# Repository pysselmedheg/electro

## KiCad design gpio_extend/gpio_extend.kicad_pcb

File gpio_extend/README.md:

# GPIO Extender

This is a gpio extender using the good ol' trick with a 74xx595 shift register for output, and 74xx165 shift register for input. The intended usage is as debug output for a Raspberry Pi Pico, but it can of course be used with other mcus.

## GP Output

The output is (up to) 32 bit, arranged as 4 bytes. There is a R2R-DAC for each byte and a pin socket with the byte as digital and analog. There is also a LED for each bit.

## GP Input

The input is (up to) 32 bit, arranged as 4 bytes. Each byte has a pin socket, and a jumper to set pull up or down for the byte.

## Serial interface

The serial interface has four digital pins:
  - pclk    : frame sync
  - sclk    : serial clock
  - ser_in  : input into the gpio extender (for GPO)
  - ser_out : output from the gpio extender (for GPI)

Negative edge on pclk:
  - GPIs are sampled.
  
Positive edge on sclk:
  - GPI data is shifted out from the GPIO extender.
  - GPO data is shifted in to the GPIO extender.
  
Positive edge on pclk:
  - GPOs are updated with new data.

## Python Driver

The python folder contains a driver for Micropython on Raspberry Pi Pico. It uses two state machines in a PIO for the communication.
Surprisingly, it can handle the interface at cpu_clk/3 bps, ie 125MHz/3 = 41.7 MHz. 

TODO: Description of driver. Until then RTFS.

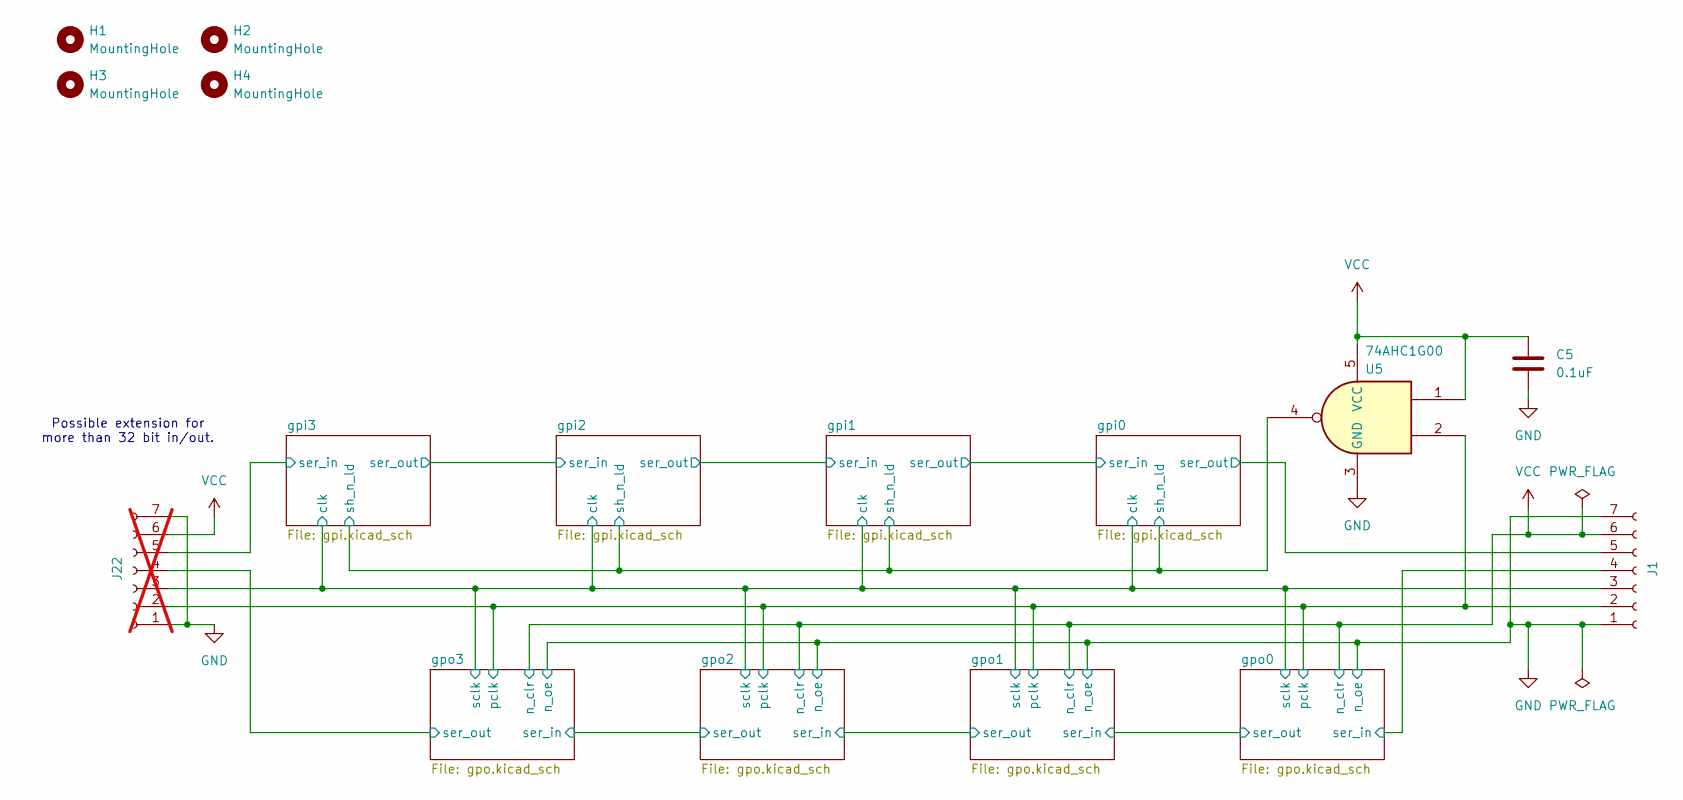
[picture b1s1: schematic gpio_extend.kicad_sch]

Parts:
C5: 0.1uF; C_0603_1608Metric_Pad1.08x0.95mm_HandSolder
H1, H2, H3, H4: MountingHole; MountingHole_3.2mm_M3
J1: Conn_01x07_Socket; PinSocket_1x07_P2.54mm_Vertical
J22: Conn_01x07_Socket; PinSocket_1x07_P2.54mm_Vertical; not fitted
U5: 74AHC1G00; SOT-23-5_HandSoldering

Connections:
/gpi0/clk: J1.3, J22.3; also elsewhere on the board
/gpi0/ser_out: J1.5; also elsewhere on the board
/gpi0/sh_n_ld: U5.4; also elsewhere on the board
/gpi3/ser_in: J22.5; also elsewhere on the board
/gpo0/pclk: J1.2, J22.2, U5.2; also elsewhere on the board
/gpo0/ser_in: J1.4; also elsewhere on the board
/gpo3/ser_out: J22.4; also elsewhere on the board
GND: C5.2, J1.1, J1.7, J22.1, J22.7, U5.3 (GND); also elsewhere on the board
VCC: C5.1, J1.6, J22.6, U5.1, U5.5 (VCC); also elsewhere on the board

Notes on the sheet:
Possible extension for more than 32 bit in/out.

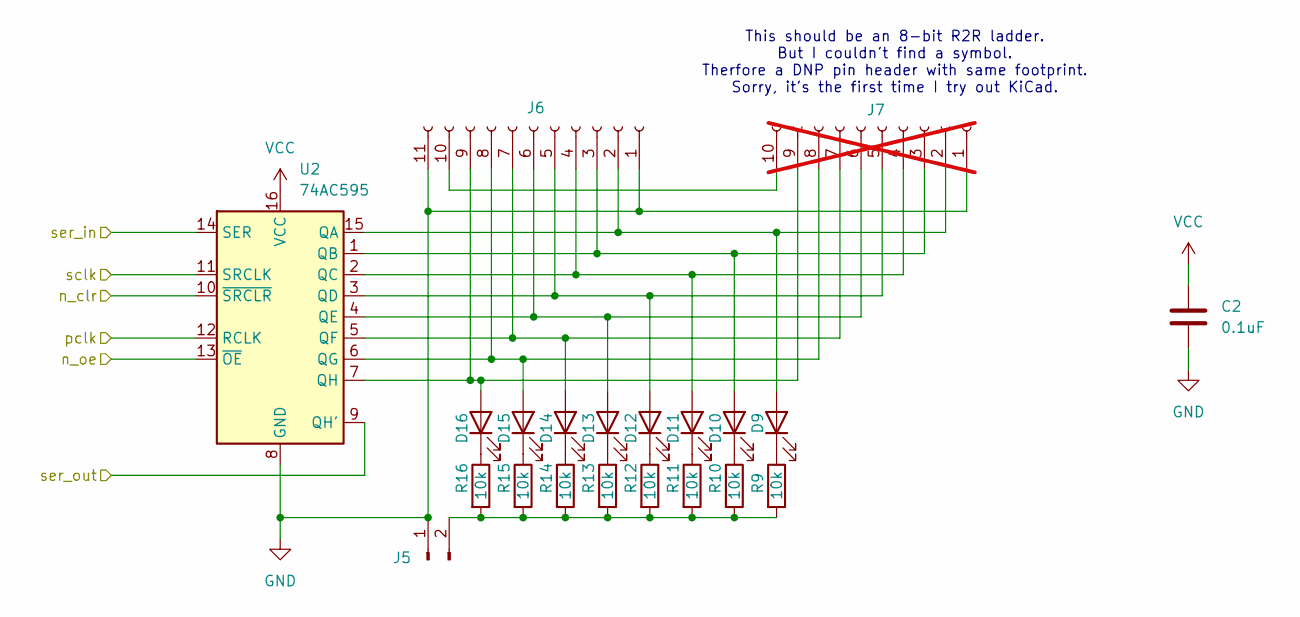
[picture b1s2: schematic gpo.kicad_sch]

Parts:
C2: 0.1uF; C_0603_1608Metric_Pad1.08x0.95mm_HandSolder
D9, D10, D11, D12, D13, D14, D15, D16: LED; LED_0603_1608Metric_Pad1.05x0.95mm_HandSolder
J5: Conn_01x02_Pin; PinHeader_1x02_P2.54mm_Vertical
J6: Conn_01x11_Socket; PinSocket_1x11_P2.54mm_Vertical
J7: Conn_01x10_Socket; PinSocket_1x10_P2.54mm_Vertical; not fitted
R9, R10, R11, R12, R13, R14, R15, R16: 10k; R_0603_1608Metric_Pad0.98x0.95mm_HandSolder
U2: 74AC595; TSSOP-16_4.4x5mm_P0.65mm

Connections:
/gpi0/clk: U2.11 (SRCLK); also elsewhere on the board
/gpo0/pclk: U2.12 (RCLK); also elsewhere on the board
/gpo0/ser_out: U2.14 (SER); also elsewhere on the board
/gpo1/ser_out: U2.9 (QH'); also elsewhere on the board
GND: C2.2, J5.1, J6.1, J6.11, J7.1, U2.8 (GND), U2.13 (~OE); also elsewhere on the board
unnamed: D9.2 (A), J6.2, J7.2, U2.15 (QA)
unnamed: D9.1 (K), R9.1
unnamed: D10.2 (A), J6.3, J7.3, U2.1 (QB)
unnamed: D10.1 (K), R10.1
unnamed: D11.2 (A), J6.4, J7.4, U2.2 (QC)
unnamed: D11.1 (K), R11.1
unnamed: D12.2 (A), J6.5, J7.5, U2.3 (QD)
unnamed: D12.1 (K), R12.1
unnamed: D13.2 (A), J6.6, J7.6, U2.4 (QE)
unnamed: D13.1 (K), R13.1
unnamed: D14.2 (A), J6.7, J7.7, U2.5 (QF)
unnamed: D14.1 (K), R14.1
unnamed: D15.2 (A), J6.8, J7.8, U2.6 (QG)
unnamed: D15.1 (K), R15.1
unnamed: D16.2 (A), J6.9, J7.9, U2.7 (QH)
unnamed: D16.1 (K), R16.1
unnamed: J5.2, R9.2, R10.2, R11.2, R12.2, R13.2, R14.2, R15.2, R16.2
unnamed: J6.10, J7.10
VCC: C2.1, U2.10 (~SRCLR), U2.16 (VCC); also elsewhere on the board

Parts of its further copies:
C1, C3, C4: 0.1uF; C_0603_1608Metric_Pad1.08x0.95mm_HandSolder
D1, D2, D3, D4, D5, D6, D7, D8, D17, D18, D19, D20, D21, D22, D23, D24, D25, D26, D27, D28, D29, D30, D31, D32: LED; LED_0603_1608Metric_Pad1.05x0.95mm_HandSolder
J2, J8, J11: Conn_01x02_Pin; PinHeader_1x02_P2.54mm_Vertical
J3, J9, J12: Conn_01x11_Socket; PinSocket_1x11_P2.54mm_Vertical
J4, J10, J13: Conn_01x10_Socket; PinSocket_1x10_P2.54mm_Vertical; not fitted
R1, R2, R3, R4, R5, R6, R7, R8, R17, R18, R19, R20, R21, R22, R23, R24, R25, R26, R27, R28, R29, R30, R31, R32: 10k; R_0603_1608Metric_Pad0.98x0.95mm_HandSolder
U1, U3, U4: 74AC595; TSSOP-16_4.4x5mm_P0.65mm

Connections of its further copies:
/gpi0/clk: U1.11 (SRCLK), U3.11 (SRCLK), U4.11 (SRCLK); also elsewhere on the board
/gpo0/pclk: U1.12 (RCLK), U3.12 (RCLK), U4.12 (RCLK); also elsewhere on the board
/gpo0/ser_in: U1.14 (SER); also elsewhere on the board
/gpo0/ser_out: U1.9 (QH'); also elsewhere on the board
/gpo1/ser_out: U3.14 (SER); also elsewhere on the board
/gpo2/ser_out: U3.9 (QH'), U4.14 (SER)
/gpo3/ser_out: U4.9 (QH'); also elsewhere on the board
GND: C1.2, C3.2, C4.2, J2.1, J3.1, J3.11, J4.1, J8.1, J9.1, J9.11, J10.1, J11.1, J12.1, J12.11, J13.1, U1.8 (GND), U1.13 (~OE), U3.8 (GND), U3.13 (~OE), U4.8 (GND), U4.13 (~OE); also elsewhere on the board
unnamed: D1.2 (A), J3.2, J4.2, U1.15 (QA)
unnamed: D1.1 (K), R1.1
unnamed: D2.2 (A), J3.3, J4.3, U1.1 (QB)
unnamed: D2.1 (K), R2.1
unnamed: D3.2 (A), J3.4, J4.4, U1.2 (QC)
unnamed: D3.1 (K), R3.1
unnamed: D4.2 (A), J3.5, J4.5, U1.3 (QD)
unnamed: D4.1 (K), R4.1
unnamed: D5.2 (A), J3.6, J4.6, U1.4 (QE)
unnamed: D5.1 (K), R5.1
unnamed: D6.2 (A), J3.7, J4.7, U1.5 (QF)
unnamed: D6.1 (K), R6.1
unnamed: D7.2 (A), J3.8, J4.8, U1.6 (QG)
unnamed: D7.1 (K), R7.1
unnamed: D8.2 (A), J3.9, J4.9, U1.7 (QH)
unnamed: D8.1 (K), R8.1
unnamed: D17.2 (A), J9.2, J10.2, U3.15 (QA)
unnamed: D17.1 (K), R17.1
unnamed: D18.2 (A), J9.3, J10.3, U3.1 (QB)
unnamed: D18.1 (K), R18.1
unnamed: D19.2 (A), J9.4, J10.4, U3.2 (QC)
unnamed: D19.1 (K), R19.1
unnamed: D20.2 (A), J9.5, J10.5, U3.3 (QD)
unnamed: D20.1 (K), R20.1
unnamed: D21.2 (A), J9.6, J10.6, U3.4 (QE)
unnamed: D21.1 (K), R21.1
unnamed: D22.2 (A), J9.7, J10.7, U3.5 (QF)
unnamed: D22.1 (K), R22.1
unnamed: D23.2 (A), J9.8, J10.8, U3.6 (QG)
unnamed: D23.1 (K), R23.1
unnamed: D24.2 (A), J9.9, J10.9, U3.7 (QH)
unnamed: D24.1 (K), R24.1
unnamed: D25.2 (A), J12.2, J13.2, U4.15 (QA)
unnamed: D25.1 (K), R25.1
unnamed: D26.2 (A), J12.3, J13.3, U4.1 (QB)
unnamed: D26.1 (K), R26.1
unnamed: D27.2 (A), J12.4, J13.4, U4.2 (QC)
unnamed: D27.1 (K), R27.1
unnamed: D28.2 (A), J12.5, J13.5, U4.3 (QD)
unnamed: D28.1 (K), R28.1
unnamed: D29.2 (A), J12.6, J13.6, U4.4 (QE)
unnamed: D29.1 (K), R29.1
unnamed: D30.2 (A), J12.7, J13.7, U4.5 (QF)
unnamed: D30.1 (K), R30.1
unnamed: D31.2 (A), J12.8, J13.8, U4.6 (QG)
unnamed: D31.1 (K), R31.1
unnamed: D32.2 (A), J12.9, J13.9, U4.7 (QH)
unnamed: D32.1 (K), R32.1
unnamed: J2.2, R1.2, R2.2, R3.2, R4.2, R5.2, R6.2, R7.2, R8.2
unnamed: J3.10, J4.10
unnamed: J8.2, R17.2, R18.2, R19.2, R20.2, R21.2, R22.2, R23.2, R24.2
unnamed: J9.10, J10.10
unnamed: J11.2, R25.2, R26.2, R27.2, R28.2, R29.2, R30.2, R31.2, R32.2
unnamed: J12.10, J13.10
VCC: C1.1, C3.1, C4.1, U1.10 (~SRCLR), U1.16 (VCC), U3.10 (~SRCLR), U3.16 (VCC), U4.10 (~SRCLR), U4.16 (VCC); also elsewhere on the board

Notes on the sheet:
This should be an 8-bit R2R ladder. But I couldn't find a symbol. Therfore a DNP pin header with same footprint. Sorry, it's the first time I try out KiCad.

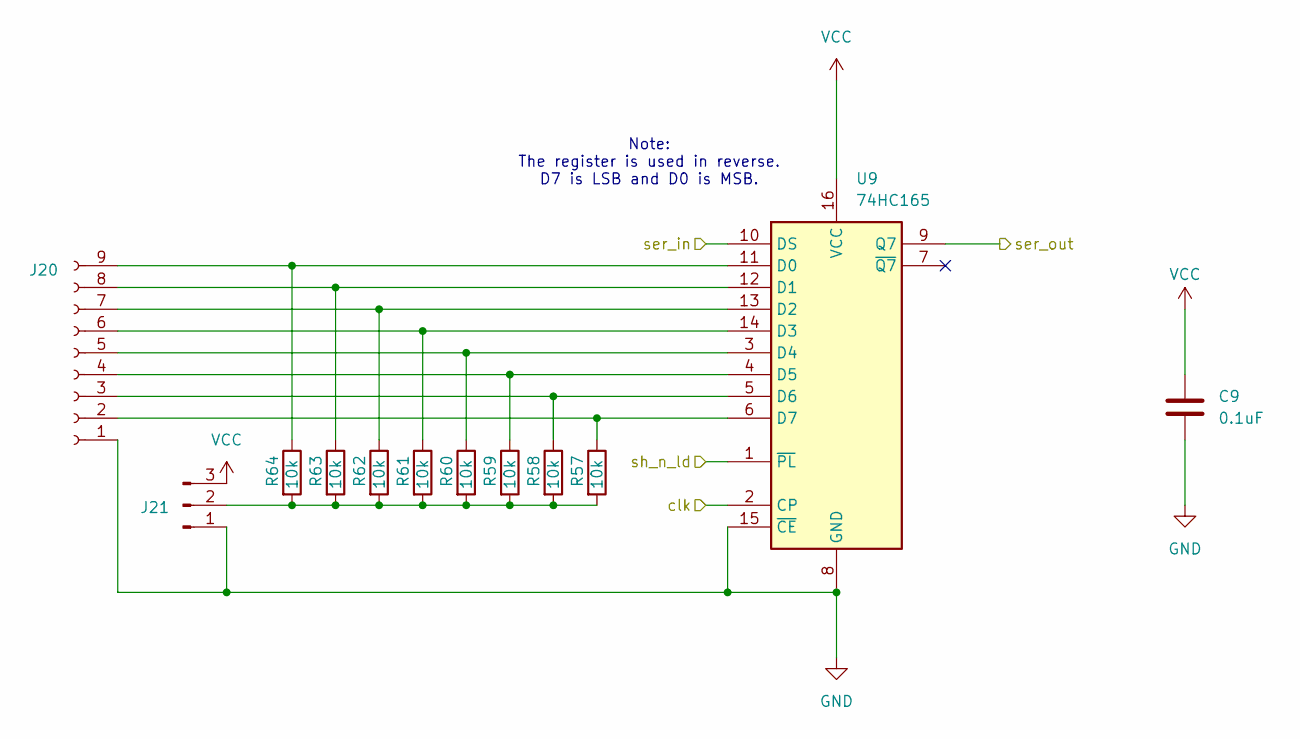
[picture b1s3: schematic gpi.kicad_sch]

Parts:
C9: 0.1uF; C_0603_1608Metric_Pad1.08x0.95mm_HandSolder
J20: Conn_01x09_Socket; PinSocket_1x09_P2.54mm_Vertical
J21: Conn_01x03_Pin; PinHeader_1x03_P2.54mm_Vertical
R57, R58, R59, R60, R61, R62, R63, R64: 10k; R_0603_1608Metric_Pad0.98x0.95mm_HandSolder
U9: 74HC165; TSSOP-16_4.4x5mm_P0.65mm

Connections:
/gpi0/clk: U9.2 (CP); also elsewhere on the board
/gpi0/sh_n_ld: U9.1 (~PL); also elsewhere on the board
/gpi2/ser_in: U9.9 (Q7); also elsewhere on the board
/gpi3/ser_in: U9.10 (DS); also elsewhere on the board
GND: C9.2, J20.1, J21.1, U9.8 (GND), U9.15 (~CE); also elsewhere on the board
unnamed: J20.2, R57.1, U9.6 (D7)
unnamed: J20.3, R58.1, U9.5 (D6)
unnamed: J20.4, R59.1, U9.4 (D5)
unnamed: J20.5, R60.1, U9.3 (D4)
unnamed: J20.6, R61.1, U9.14 (D3)
unnamed: J20.7, R62.1, U9.13 (D2)
unnamed: J20.8, R63.1, U9.12 (D1)
unnamed: J20.9, R64.1, U9.11 (D0)
unnamed: J21.2, R57.2, R58.2, R59.2, R60.2, R61.2, R62.2, R63.2, R64.2
VCC: C9.1, J21.3, U9.16 (VCC); also elsewhere on the board

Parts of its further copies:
C6, C7, C8: 0.1uF; C_0603_1608Metric_Pad1.08x0.95mm_HandSolder
J14, J16, J18: Conn_01x09_Socket; PinSocket_1x09_P2.54mm_Vertical
J15, J17, J19: Conn_01x03_Pin; PinHeader_1x03_P2.54mm_Vertical
R33, R34, R35, R36, R37, R38, R39, R40, R41, R42, R43, R44, R45, R46, R47, R48, R49, R50, R51, R52, R53, R54, R55, R56: 10k; R_0603_1608Metric_Pad0.98x0.95mm_HandSolder
U6, U7, U8: 74HC165; TSSOP-16_4.4x5mm_P0.65mm

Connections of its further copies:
/gpi0/clk: U6.2 (CP), U7.2 (CP), U8.2 (CP); also elsewhere on the board
/gpi0/ser_in: U6.10 (DS), U7.9 (Q7)
/gpi0/ser_out: U6.9 (Q7); also elsewhere on the board
/gpi0/sh_n_ld: U6.1 (~PL), U7.1 (~PL), U8.1 (~PL); also elsewhere on the board
/gpi1/ser_in: U7.10 (DS), U8.9 (Q7)
/gpi2/ser_in: U8.10 (DS); also elsewhere on the board
GND: C6.2, C7.2, C8.2, J14.1, J15.1, J16.1, J17.1, J18.1, J19.1, U6.8 (GND), U6.15 (~CE), U7.8 (GND), U7.15 (~CE), U8.8 (GND), U8.15 (~CE); also elsewhere on the board
unnamed: J14.2, R33.1, U6.6 (D7)
unnamed: J14.3, R34.1, U6.5 (D6)
unnamed: J14.4, R35.1, U6.4 (D5)
unnamed: J14.5, R36.1, U6.3 (D4)
unnamed: J14.6, R37.1, U6.14 (D3)
unnamed: J14.7, R38.1, U6.13 (D2)
unnamed: J14.8, R39.1, U6.12 (D1)
unnamed: J14.9, R40.1, U6.11 (D0)
unnamed: J15.2, R33.2, R34.2, R35.2, R36.2, R37.2, R38.2, R39.2, R40.2
unnamed: J16.2, R41.1, U7.6 (D7)
unnamed: J16.3, R42.1, U7.5 (D6)
unnamed: J16.4, R43.1, U7.4 (D5)
unnamed: J16.5, R44.1, U7.3 (D4)
unnamed: J16.6, R45.1, U7.14 (D3)
unnamed: J16.7, R46.1, U7.13 (D2)
unnamed: J16.8, R47.1, U7.12 (D1)
unnamed: J16.9, R48.1, U7.11 (D0)
unnamed: J17.2, R41.2, R42.2, R43.2, R44.2, R45.2, R46.2, R47.2, R48.2
unnamed: J18.2, R49.1, U8.6 (D7)
unnamed: J18.3, R50.1, U8.5 (D6)
unnamed: J18.4, R51.1, U8.4 (D5)
unnamed: J18.5, R52.1, U8.3 (D4)
unnamed: J18.6, R53.1, U8.14 (D3)
unnamed: J18.7, R54.1, U8.13 (D2)
unnamed: J18.8, R55.1, U8.12 (D1)
unnamed: J18.9, R56.1, U8.11 (D0)
unnamed: J19.2, R49.2, R50.2, R51.2, R52.2, R53.2, R54.2, R55.2, R56.2
VCC: C6.1, C7.1, C8.1, J15.3, J17.3, J19.3, U6.16 (VCC), U7.16 (VCC), U8.16 (VCC); also elsewhere on the board

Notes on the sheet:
Note: The register is used in reverse. D7 is LSB and D0 is MSB.

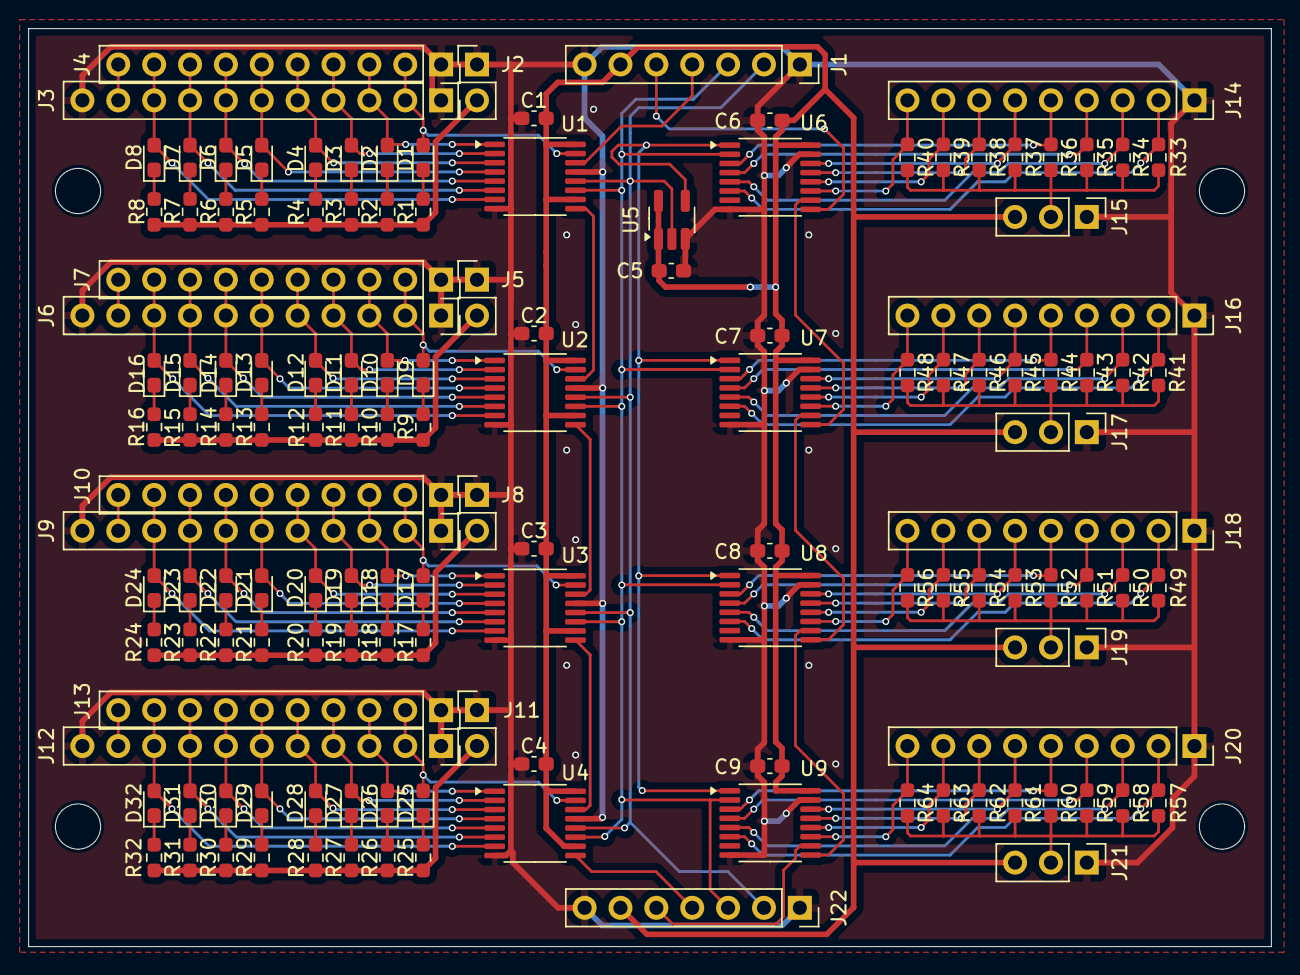
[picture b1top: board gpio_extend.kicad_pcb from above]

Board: 2 copper layers, 88.0 x 65.0 mm, 140 parts (0 on the bottom side), 123 nets.

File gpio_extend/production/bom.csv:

Designator,Footprint,Quantity,Value,LCSC Part #
"C1, C2, C3, C4, C5, C6, C7, C8, C9",0603,9,0.1uF,
"D1, D10, D11, D12, D13, D14, D15, D16, D17, D18, D19, D2, D20, D21, D22, D23, D24, D25, D26, D27, D28, D29, D3, D30, D31, D32, D4, D5, D6, D7, D8, D9",0603,32,LED,
"J1, J22",PinSocket_1x07_P2.54mm_Vertical,2,Conn_01x07_Socket,
"J11, J2, J5, J8",PinHeader_1x02_P2.54mm_Vertical,4,Conn_01x02_Pin,
"J12, J3, J6, J9",PinSocket_1x11_P2.54mm_Vertical,4,Conn_01x11_Socket,
"J14, J16, J18, J20",PinSocket_1x09_P2.54mm_Vertical,4,Conn_01x09_Socket,
"J15, J17, J19, J21",PinHeader_1x03_P2.54mm_Vertical,4,Conn_01x03_Pin,
"R1, R10, R11, R12, R13, R14, R15, R16, R17, R18, R19, R2, R20, R21, R22, R23, R24, R25, R26, R27, R28, R29, R3, R30, R31, R32, R33, R34, R35, R36, R37, R38, R39, R4, R40, R41, R42, R43, R44, R45, R46, R47, R48, R49, R5, R50, R51, R52, R53, R54, R55, R56, R57, R58, R59, R6, R60, R61, R62, R63, R64, R7, R8, R9",0603,64,10k,
"U1, U2, U3, U4",TSSOP-16_4.4x5mm_P0.65mm,4,74AC595,
U5,SOT-23-5_HandSoldering,1,74AHC1G00,
"U6, U7, U8, U9",TSSOP-16_4.4x5mm_P0.65mm,4,74HC165,

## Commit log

2025-01-16 Added gpio_extend
2025-01-22 Final for production
2025-02-17 Python driver for gpio extender
2025-02-18 Added gpio_extend README.md
